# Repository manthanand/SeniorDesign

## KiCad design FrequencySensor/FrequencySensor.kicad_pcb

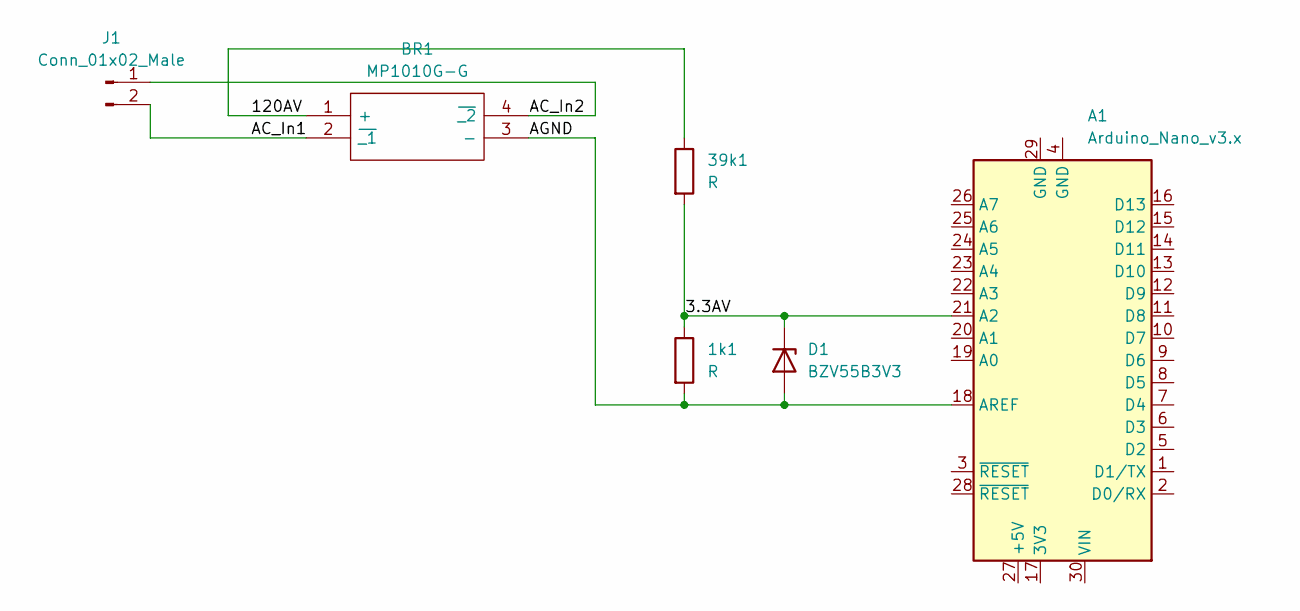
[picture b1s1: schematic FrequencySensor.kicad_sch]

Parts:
1k1, 39k1: R; R_Axial_DIN0204_L3.6mm_D1.6mm_P1.90mm_Vertical
A1: Arduino_Nano_v3.x; Arduino_Nano
BR1: MP1010G-G; DIP1270W130P1270L1905H780Q4N; Mouser Part Number 750-MP1010G-G
D1: BZV55B3V3; D_MiniMELF
J1: Conn_01x02_Male; Molex_Mega-Fit_76829-0002_2x01_P5.70mm_Vertical

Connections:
/3.3AV: 1k1.1, 39k1.2, A1.21 (A2), D1.1 (K)
/120AV: 39k1.1, BR1.1 (+)
/AC_In1: BR1.2 (~_1), J1.2
/AC_In2: BR1.4 (~_2), J1.1
/AGND: 1k1.2, A1.18 (AREF), BR1.3 (-), D1.2 (A)

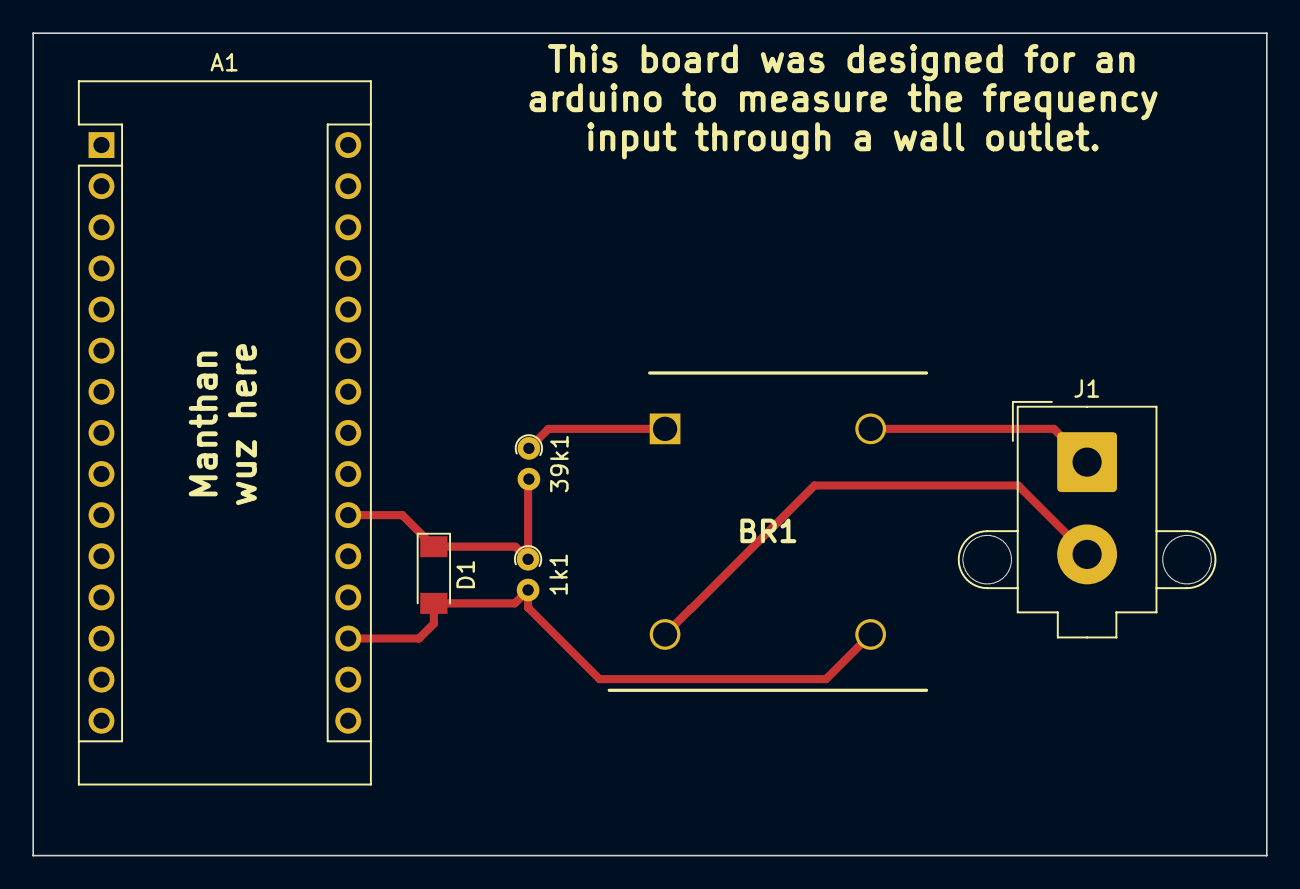
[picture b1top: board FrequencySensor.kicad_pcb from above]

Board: 2 copper layers, 76.2 x 50.8 mm, 6 parts (0 on the bottom side), 5 nets.

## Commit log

2022-03-22 Fixed frequency measurements based on doubled frequency of rectifier
2022-04-05 Created Schematic and updated code based on Evans comments
2022-04-12 Create IterativeCostFunctionSystem
2022-04-22 Created testbed in case we want to test controls with ML. Also made changes to code to account for latency
2022-04-22 added weather csv generator module
2022-07-22 Created PCB
2022-08-24 Added gerbers and designing software architecture
2022-08-24 More architecture changes
2022-08-24 Intermediate FSM and added CSV
2022-08-24 something happened. second push
2022-08-24 Finished prototype software architecture
2022-08-24 Changes according to Nora and Neeley
2022-08-29 implemented greedypick
2022-08-29 stoopid kicad sstuff
2022-08-29 changed fsm
2022-08-29 changed architecture to remove threading
2022-08-29 Add files via upload
    Now sums data from .csv and puts it into "Running Test.csv"
2022-08-31 Removed threading
2022-08-31 Added Data format
2022-08-31 Added data architecture
2022-09-07 csv interactive file (prob won't be used)
2022-09-07 finished FSM
2022-09-07 I use clusterInit for supporting the current FSM
2022-09-07 Send dictionary to all modules
2022-09-07 Use Dictionary for FSM/ML modules
2022-09-07 Create demand_ml_multiple
    Gives 15, 30, 45, and 60 minute predictions
2022-09-07 Adding support to write data for ML
2022-09-07 Restructure files
2022-09-07 Fixed serial issues
2022-09-07 returns array of current, 15, 30, 45, 60 min demand predictions
2022-09-07 Writing output data to csv
2022-09-07 Write output to file
2022-09-09 added csv writing
2022-09-12 Allowed floating point math
2022-09-14 fixed file paths
2022-09-14 Added FSM.reset function
2022-09-19 Send weather data to supply side
2022-09-19 Merged branches
2022-09-19 First Supply Upload!
    Waow
2022-09-19 awful code
2022-09-19 fixed bug re: max time_on in FSM.py
2022-09-21 fixed bug re: deletion from lists
2022-09-21 Fixed ML output data
2022-09-22 Added priority to csv
2022-09-25 Week of 9_19 updates
    Added MLP model, troubleshooting of RNN, more consistent data cleaning
2022-09-25 test pr template
2022-09-25 changed location
2022-09-26 Created demand demo
2022-09-28 corn nut dust
2022-09-28 adding battery functionality
2022-09-28 Added requirements.txt and removed unnecessary csv's
2022-09-28 Python places files in working directory now
2022-09-29 Added more demand data
2022-10-03 Removed serial readings
2022-10-03 removed unneeded data
2022-10-03 removed info from tag_metadata
2022-10-03 Organized Data
2022-10-03 added battery functionality to FSM
2022-10-03 updated output data
2022-10-03 integration with new demand data
2022-10-05 Different ClusterList for every data folder
2022-10-05 Fixed bugs
2022-10-05 fixed current value in demand
2022-10-05 battery use
2022-10-05 Allowed for different ClusterList formats
2022-10-05 finish demand solo demo on new data
2022-10-05 Changed Cluster List to fit format
2022-10-05 Removed 15 minute data
2022-10-05 full system test done
2022-10-05 Removed Runs
2022-10-05 integration test :)
2022-10-05 internalized the iterator
2022-10-06 changes for ability to run on new data and demo
2022-10-10 bugfix
2022-10-10 Tuning and boomin
    Hyaaa
2022-10-10 Allow for customizable number of time horizons
2022-10-12 Added priorities to clusterlist.csv files. Also made it so LSTM model doesn't retrain
2022-10-12 Redid main.py and demand.py
2022-10-12 MLP Bugfixes
    Dropped index, memory data in SolarTrainingData has been fixed
2022-10-12 Fixed more bugs
2022-10-17 bugs n custom loss
    ska
2022-10-17 attempting to batch
2022-10-17 Update demand ml to save and load model instead of retrain
2022-10-17 ML now trains once and uses old model
2022-10-19 Made some models and saved them. Also added counter for batch updating models
2022-10-19 LSTM update
    Working through the new cost function
2022-10-19 Updated accuracy calculations in demand.py
2022-10-19 Fix bugs
2022-10-19 LSTM Custom Function
    Added custom function that does the same thing as MSE loss function (confirmed with testing)
2022-10-19 demand.py update with test
2022-10-23 Processed all data in csv's to remove additive wattage per day
2022-10-23 prevent test_demonstration from running
2022-10-23 Updated test
2022-10-23 get_new_data to ignore nulls in csvs
2022-10-23 Removed CSV's with no data in them
2022-10-23 Added preprocessed folders
2022-10-23 Removed ending rows
2022-10-23 Processed Data with -1 for null values
2022-10-24 Removed models from Processed folders
2022-10-25 updated MLP and many-to-one lstm attempt
2022-10-25 mlp update
2022-10-26 Bug fixes
2022-10-26 added underpredict/overpredict values
2022-10-26 Removed zeros from cluster data
2022-10-27 Testing ML
2022-10-31 Added accuracy stuff
2022-10-31 added new python script for many to one
2022-10-31 added new python script
2022-10-31 i hate u jupyter notebook
2022-10-31 Epoch Graph
    hehe
2022-10-31 Re preprocess data
2022-10-31 Preprocessed data and collected new graph
2022-10-31 fixed fsm bug
2022-11-01 Bigger Data Sets
    Improved data cleaning process and got new weather months to get bigger data set
2022-11-01 Custom Loss Implementation
    Added custom loss and evaluation metric to LSTM model
2022-11-01 Created models for multiple numbers of epochs and found accuracy for every tenth increase
2022-11-02 Created models for 2018 on 5000 data points and 2020 on 1500 data points.
2022-11-02 preliminary integration of supply
2022-11-02 Refactored Supply ML Module
    Added notebook to be integrated with FSM called Supply ML Module
2022-11-05 Custom Loss LSTM Testing
    Validated results using holdout set
2022-11-07 Cleared Output
    neva crash
2022-11-07 full supply excels for cleaning
2022-11-07 integrated supply + FSM change
2022-11-07 2018 Cleaned Weather Data
    itsu clean
2022-11-08 push for manth
2022-11-09 scree
2022-11-09 Normalized data
    normalized and rando changes
2022-11-09 Cleared nans
    dropped nans
2022-11-09 for evan
2022-11-09 fixed ml
2022-11-09 Datasets Galore
    Data good me like data
2022-11-09 lstm integration
2022-11-12 More Data Less Problems
    Increased data for all aggregated datasets
2022-11-13 fixed(?) negative supply bug
2022-11-15 Demo Day Updates
    Last second tweaks for demo day graphs
2022-11-15 Code Cleanup. Repository Cleanup
2022-11-15 More code cleanup
2022-11-15 Cleaned FSM code
2022-11-16 final demo
2022-12-09 todo notes in fsm
2024-06-12 Revert "Merge branch 'main' of https://github.com/manthanand/SeniorDesign"
    This reverts commit ae17cae60c7a34a6a34e399cc17dcd95fcec394f, reversing
    changes made to e181e9fa39151c9cb70a526fc6d3666d3597b989.
